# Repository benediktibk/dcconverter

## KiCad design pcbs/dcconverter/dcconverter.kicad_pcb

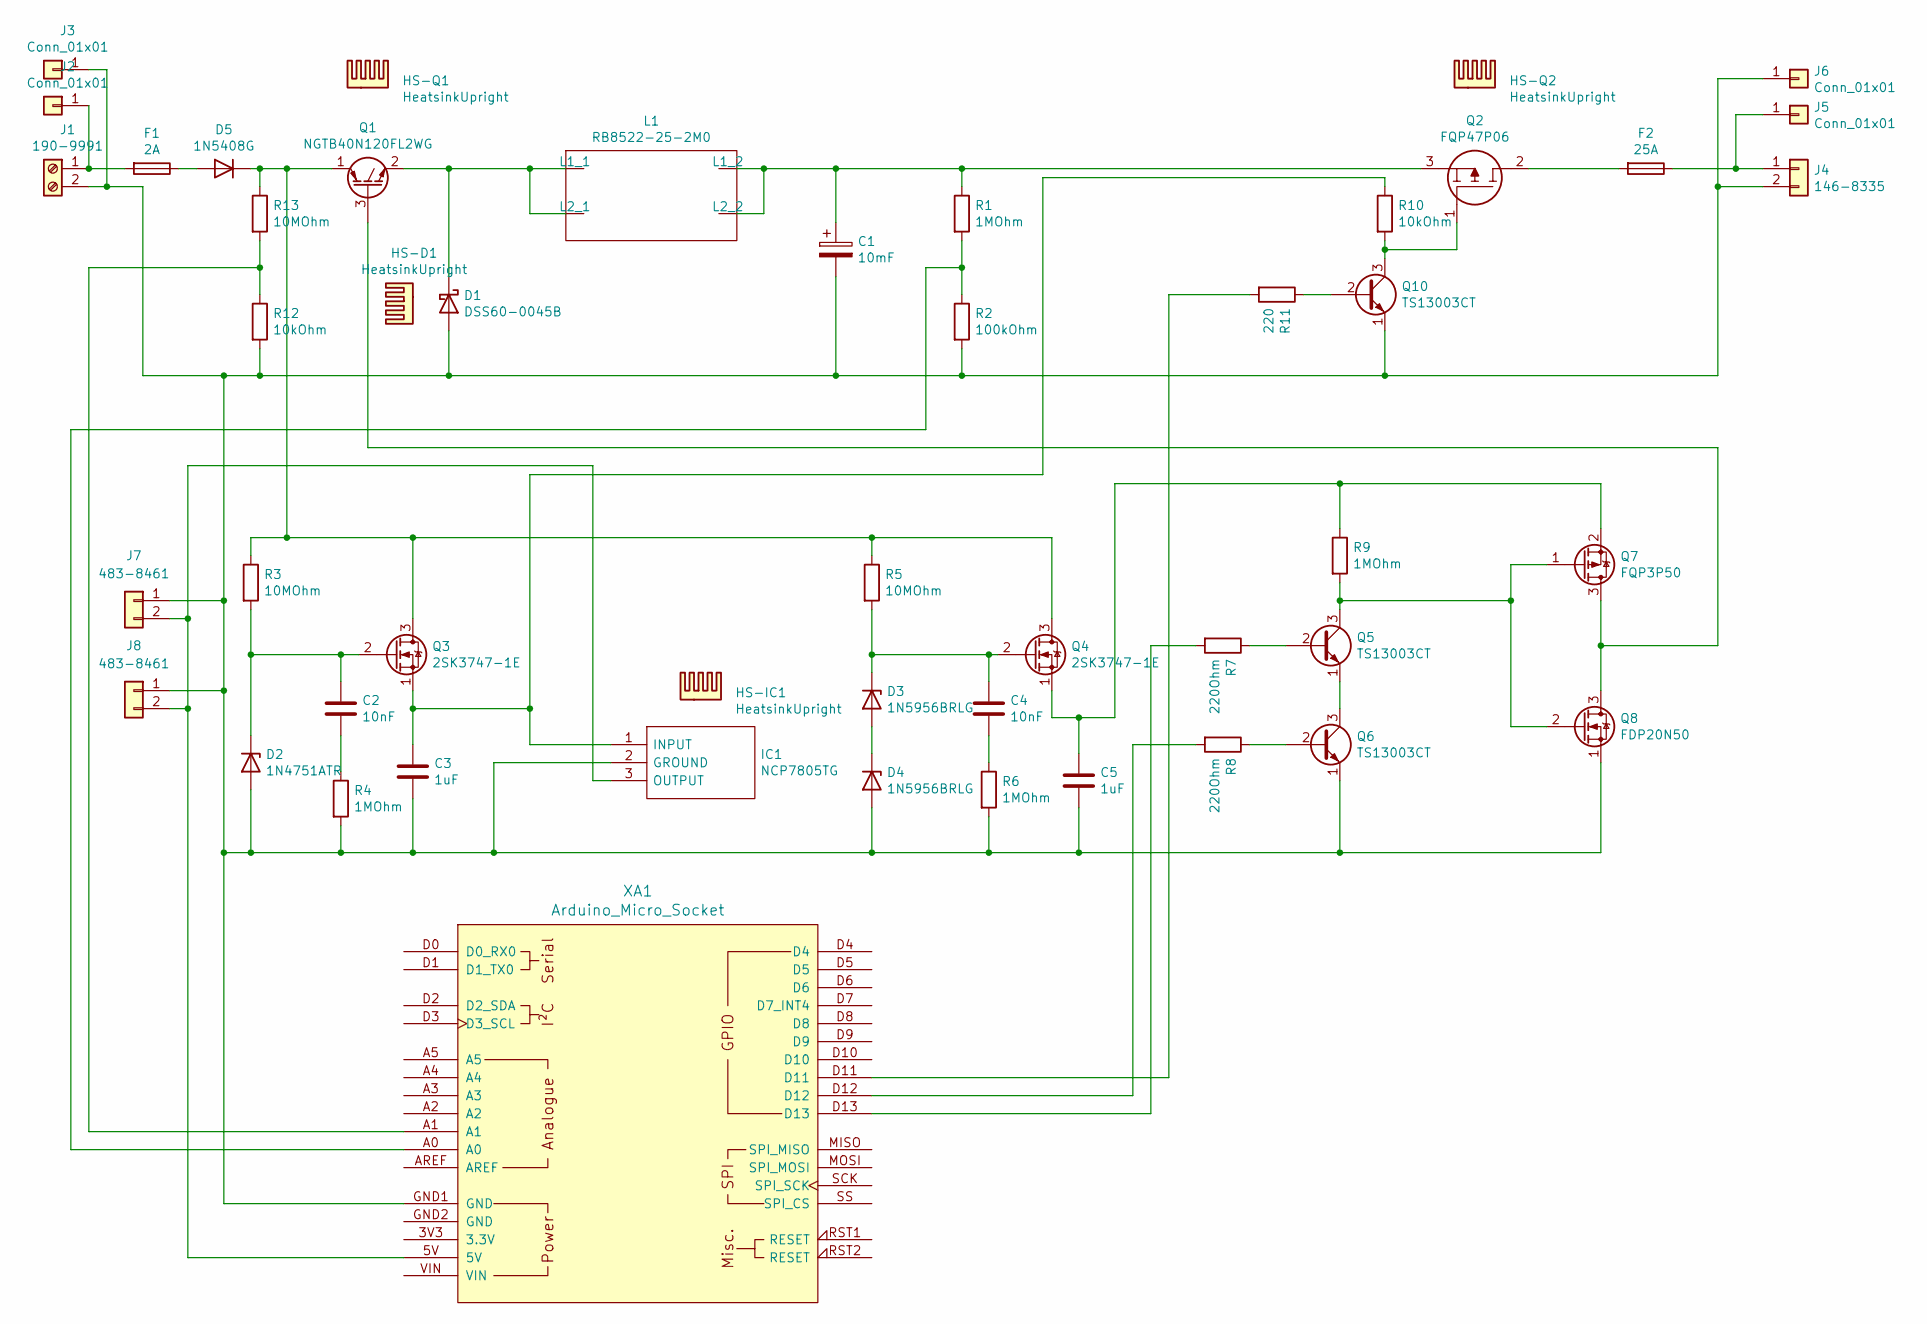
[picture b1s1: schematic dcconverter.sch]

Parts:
C1: 10mF; CAPPRD1250W100D2550H5200
C2, C4: 10nF; C_Disc_D14.5mm_W5.0mm_P7.50mm
C3, C5: 1uF; CP_Radial_D8.0mm_P2.50mm
D1: DSS60-0045B; DSS60-0045B_Vertical
D2: 1N4751ATR; D_DO-41_SOD81_P10.16mm_Horizontal
D3, D4: 1N5956BRLG; D_DO-41_SOD81_P10.16mm_Horizontal
D5: 1N5408G
F1: 2A; Fuseholder_Cylinder-5x20mm_Schurter_0031_8201_Horizontal_Op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
F2: 25A; Fuseholder_Cylinder-5x20mm_Schurter_0031_8201_Horizontal_Op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
HS-D1: HeatsinkUpright
HS-IC1: HeatsinkUpright
HS-Q1, HS-Q2: HeatsinkUpright
IC1: NCP7805TG; TO-220-3_Vertical; Manufacturer_Part_Number NCP7805TG
J1: 190-9991; TerminalBlock_2pin_10mm
J2, J3, J5, J6: Conn_01x01; SLB4-I90
J4: 146-8335; connector_2pin_P10.6mm
J7, J8: 483-8461; Molex_KK_254_2pin
L1: RB8522-25-2M0; rb8522_size5
Q1: NGTB40N120FL2WG; NGTB40N120FL2WG_Vertical
Q2: FQP47P06; FQP47P06_Vertical_Wide; Manufacturer_Part_Number FQP47P06
Q3, Q4: 2SK3747-1E; 2SK3747_TabDown
Q5, Q6, Q10: TS13003CT; TS13003CT_wide
Q7: FQP3P50; FQP3P50_Horizontal_TabDown
Q8: FDP20N50; FDP20N50_Horizontal_TabDown
R1, R4, R6, R9: 1MOhm; R_Axial_DIN0207_L6.3mm_D2.5mm_P10.16mm_Horizontal
R2: 100kOhm; R_Axial_DIN0207_L6.3mm_D2.5mm_P10.16mm_Horizontal
R3, R5, R13: 10MOhm; R_Axial_DIN0207_L6.3mm_D2.5mm_P10.16mm_Horizontal
R7, R8: 220Ohm; R_Axial_DIN0207_L6.3mm_D2.5mm_P10.16mm_Horizontal
R10, R12: 10kOhm; R_Axial_DIN0207_L6.3mm_D2.5mm_P10.16mm_Horizontal
R11: 220; R_Axial_DIN0207_L6.3mm_D2.5mm_P10.16mm_Horizontal
XA1: Arduino_Micro_Socket

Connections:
unnamed: C1.1, L1.3 (L1_2), L1.4 (L2_2), Q2.3, R1.1
unnamed: C1.2, C3.2, C5.2, D1.2 (A), D2.2 (A), D4.2 (A), IC1.2 (GROUND), J1.2, J3.1, J4.2, J6.1, J7.1, J8.1, Q6.1 (E), Q8.1 (S), Q10.1 (E), R2.2, R4.2, R6.2, R12.2, XA1.GND1 (GND)
unnamed: C2.1, D2.1 (K), Q3.2 (G), R3.2
unnamed: C2.2, R4.1
unnamed: C3.1, IC1.1 (INPUT), Q3.1 (S), R10.1
unnamed: C4.1, D3.1 (K), Q4.2 (G), R5.2
unnamed: C4.2, R6.1
unnamed: C5.1, Q4.1 (S), Q7.2 (S), R9.1
unnamed: D1.1 (K), L1.1 (L1_1), L1.2 (L2_1), Q1.2 (E)
unnamed: D3.2 (A), D4.1 (K)
unnamed: D5.1 (K), Q1.1 (C), Q3.3 (D), Q4.3 (D), R3.1, R5.1, R13.1
unnamed: D5.2 (A), F1.1
unnamed: F1.2, J1.1, J2.1
unnamed: F2.1, J4.1, J5.1
unnamed: F2.2, Q2.2
unnamed: IC1.3 (OUTPUT), J7.2, J8.2, XA1.5V
unnamed: Q1.3 (G), Q7.3 (D), Q8.3 (D)
unnamed: Q5.1 (E), Q6.3 (C)
unnamed: Q5.2 (B), R7.1
unnamed: Q5.3 (C), Q7.1 (G), Q8.2 (G), R9.2
unnamed: Q6.2 (B), R8.1
unnamed: Q10.2 (B), R11.1
unnamed: Q2.1, Q10.3 (C), R10.2
unnamed: R1.2, R2.1, XA1.A0
unnamed: R7.2, XA1.D13
unnamed: R8.2, XA1.D12
unnamed: R11.2, XA1.D11
unnamed: R12.1, R13.2, XA1.A1

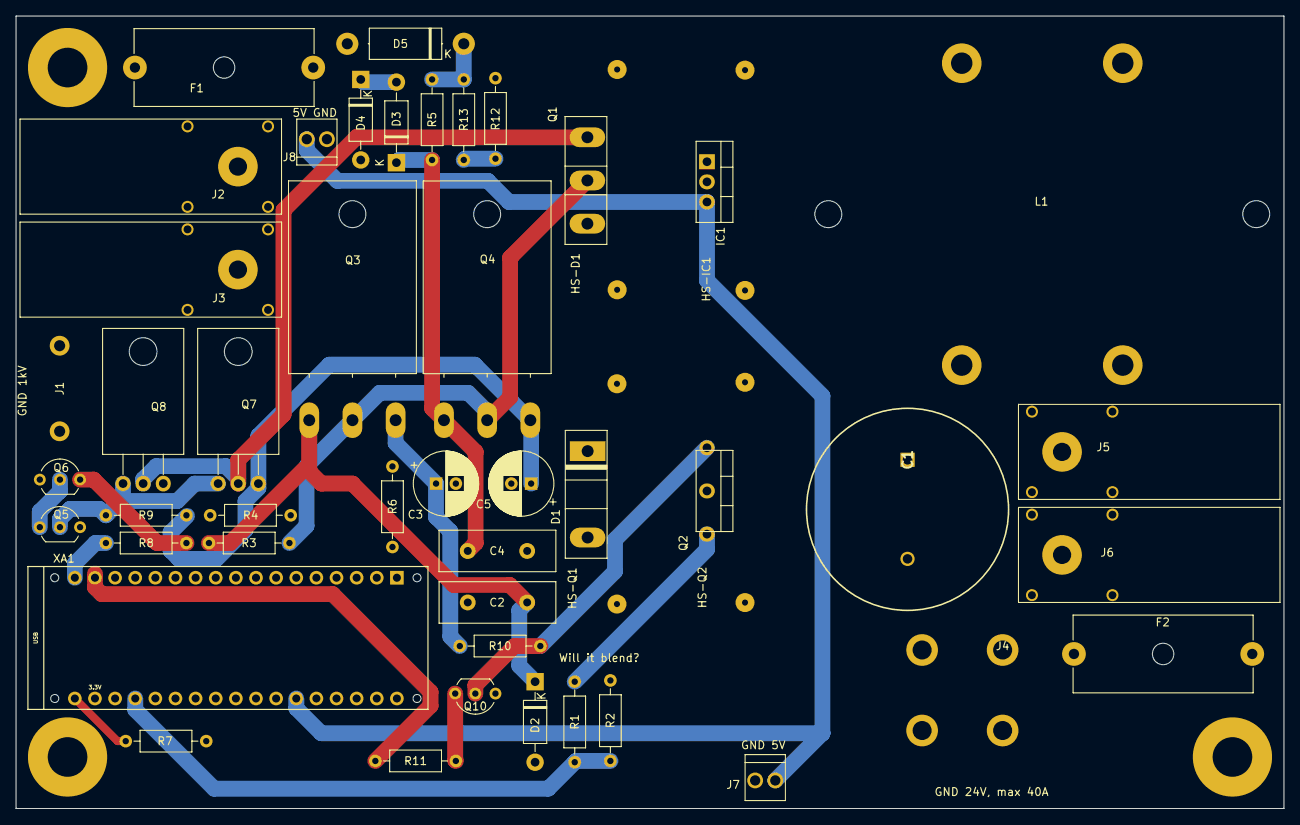
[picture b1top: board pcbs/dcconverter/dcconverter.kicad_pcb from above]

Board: 4 copper layers, 160.0 x 100.0 mm, 49 parts (0 on the bottom side), 28 nets.

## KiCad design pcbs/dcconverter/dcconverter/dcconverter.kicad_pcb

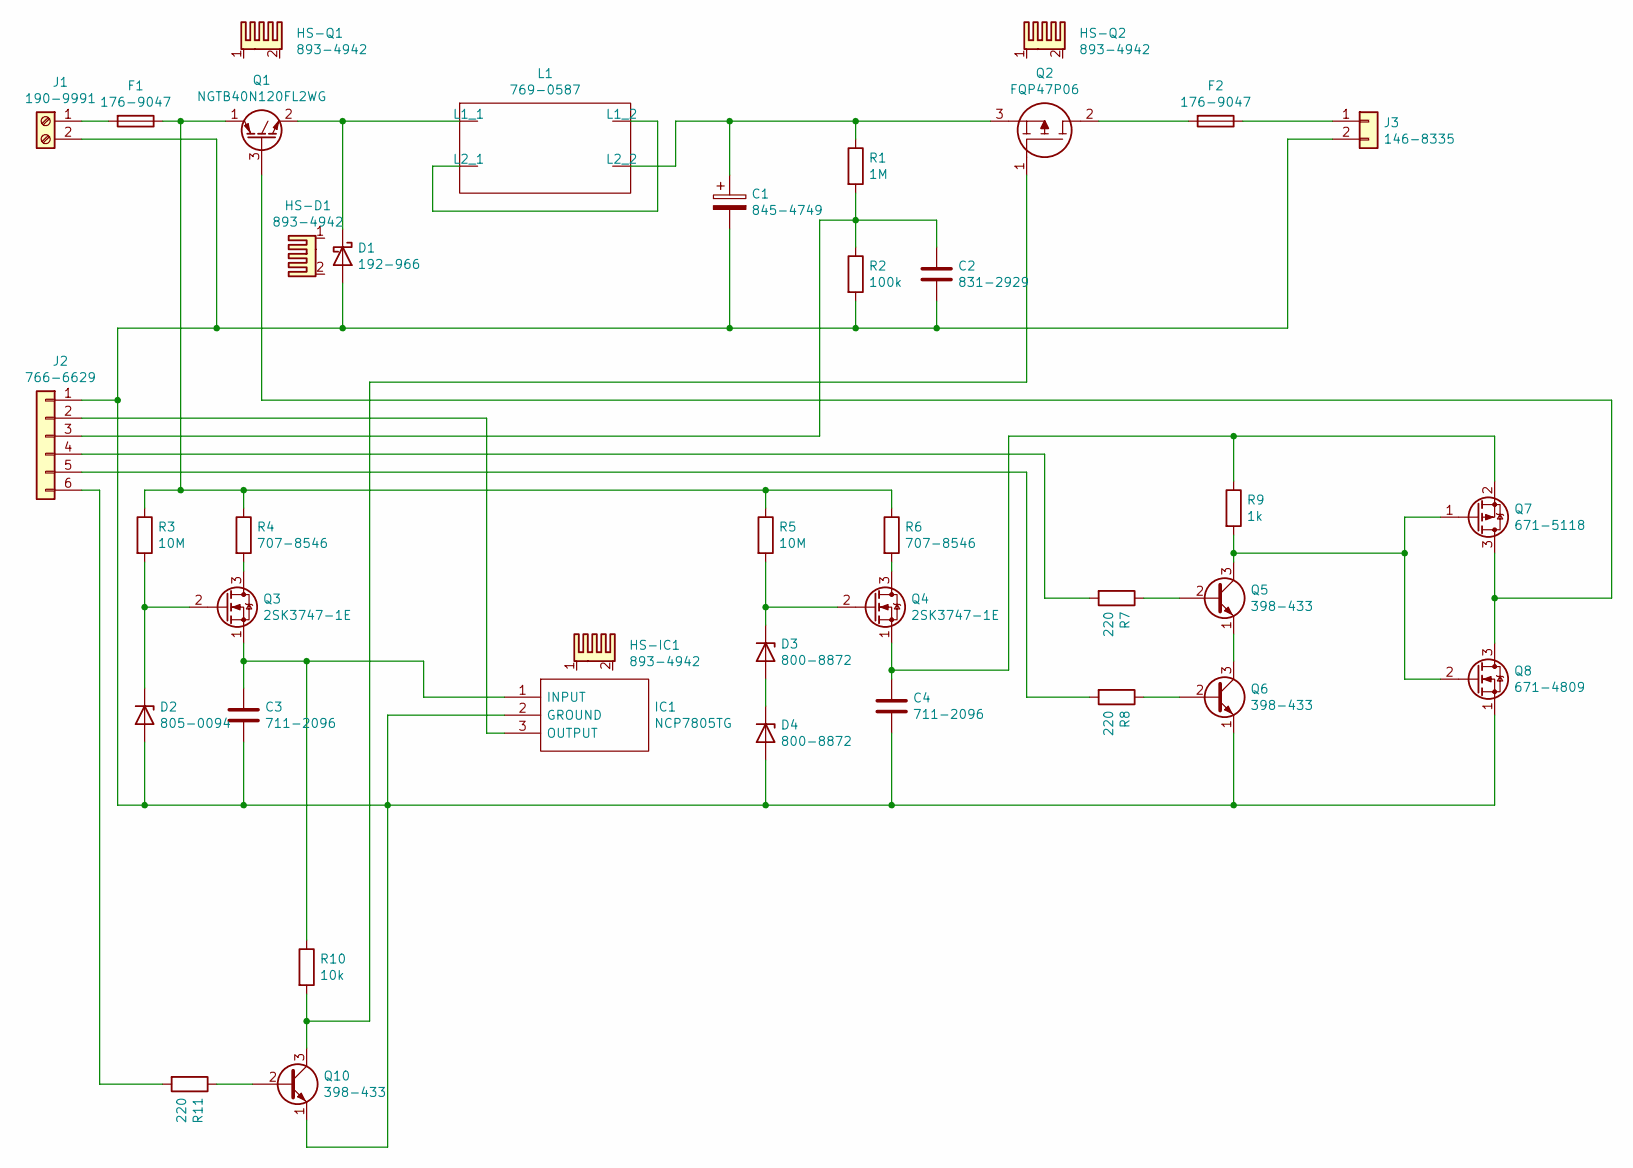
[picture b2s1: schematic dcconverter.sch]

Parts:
C1: 845-4749; CAPPRD1250W100D2550H5200
C2: 831-2929; C_Disc_D7.5mm_W5.0mm_P7.50mm
C3, C4: 711-2096; C_Disc_D7.5mm_W5.0mm_P7.50mm
D1: 192-966; D_DO-247_Vertical
D2: 805-0094; D_DO-41_SOD81_P10.16mm_Horizontal
D3, D4: 800-8872; D_DO-41_SOD81_P10.16mm_Horizontal
F1, F2: 176-9047; Fuseholder_Cylinder-5x20mm_Schurter_0031_8201_Horizontal_Op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
HS-D1: 893-4942; Heatsink_Fischer_SK129-STS_42x25mm_2xDrill2.5mm
HS-IC1: 893-4942; Heatsink_Fischer_SK129-STS_42x25mm_2xDrill2.5mm
HS-Q1, HS-Q2: 893-4942; Heatsink_Fischer_SK129-STS_42x25mm_2xDrill2.5mm
IC1: NCP7805TG; TO-220-3_Vertical; Manufacturer_Part_Number NCP7805TG
J1: 190-9991; TerminalBlock_Dinkle_DT-55-B01X-02_P10.00mm
J2: 766-6629; CES-106-XX-Y-S
J3: 146-8335; connector_2pin_P10.6mm
L1: 769-0587; rb8522_size5
Q1: NGTB40N120FL2WG; TO-247-3_Vertical
Q2: FQP47P06; TO254P483X1016X2261-3P; Manufacturer_Part_Number FQP47P06
Q3, Q4: 2SK3747-1E; TO-3P-3_Horizontal_TabDown
Q5, Q6, Q10: 398-433; TO-92_Inline
Q7: 671-5118; TO-220-3_Horizontal_TabDown
Q8: 671-4809; TO-3P-3_Horizontal_TabDown
R1: 1M; R_Axial_DIN0207_L6.3mm_D2.5mm_P10.16mm_Horizontal
R2: 100k; R_Axial_DIN0207_L6.3mm_D2.5mm_P10.16mm_Horizontal
R3, R5: 10M; R_Axial_DIN0207_L6.3mm_D2.5mm_P10.16mm_Horizontal
R4, R6: 707-8546; R_Axial_DIN0207_L6.3mm_D2.5mm_P10.16mm_Horizontal
R7, R8, R11: 220; R_Axial_DIN0207_L6.3mm_D2.5mm_P10.16mm_Horizontal
R9: 1k; R_Axial_DIN0207_L6.3mm_D2.5mm_P10.16mm_Horizontal
R10: 10k; R_Axial_DIN0207_L6.3mm_D2.5mm_P10.16mm_Horizontal

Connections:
unnamed: C1.1, L1.4 (L2_2), Q2.3, R1.1
unnamed 1: C1.2, C2.2, C3.2, C4.2, D1.2 (A), D2.2 (A), D4.2 (A), IC1.2 (GROUND), J1.2, J2.1, J3.2, Q6.1 (E), Q8.1 (S), Q10.1 (E), R2.2; also elsewhere on the board
unnamed: C2.1, J2.3, R1.2, R2.1
unnamed: C3.1, IC1.1 (INPUT), Q3.1 (S), R10.1
unnamed: C4.1, Q4.1 (S), Q7.2 (S), R9.1
unnamed: D1.1 (K), L1.1 (L1_1), Q1.2 (E)
unnamed: D2.1 (K), Q3.2 (G), R3.2
unnamed: D3.1 (K), Q4.2 (G), R5.2
unnamed: D3.2 (A), D4.1 (K)
unnamed: F1.1, Q1.1 (C), R3.1, R4.1, R5.1, R6.1
unnamed: F1.2, J1.1
unnamed: F2.1, J3.1
unnamed: F2.2, Q2.2
unnamed 17: IC1.3 (OUTPUT), J2.2; also elsewhere on the board
unnamed: J2.4, R7.2
unnamed: J2.5, R8.2
unnamed: J2.6, R11.2
unnamed: L1.2 (L2_1), L1.3 (L1_2)
unnamed: Q1.3 (G), Q7.3 (D), Q8.3 (D)
unnamed: Q3.3 (D), R4.2
unnamed: Q4.3 (D), R6.2
unnamed: Q5.1 (E), Q6.3 (C)
unnamed: Q5.2 (B), R7.1
unnamed: Q5.3 (C), Q7.1 (G), Q8.2 (G), R9.2
unnamed: Q6.2 (B), R8.1
unnamed: Q10.2 (B), R11.1
unnamed: Q2.1, Q10.3 (C), R10.2

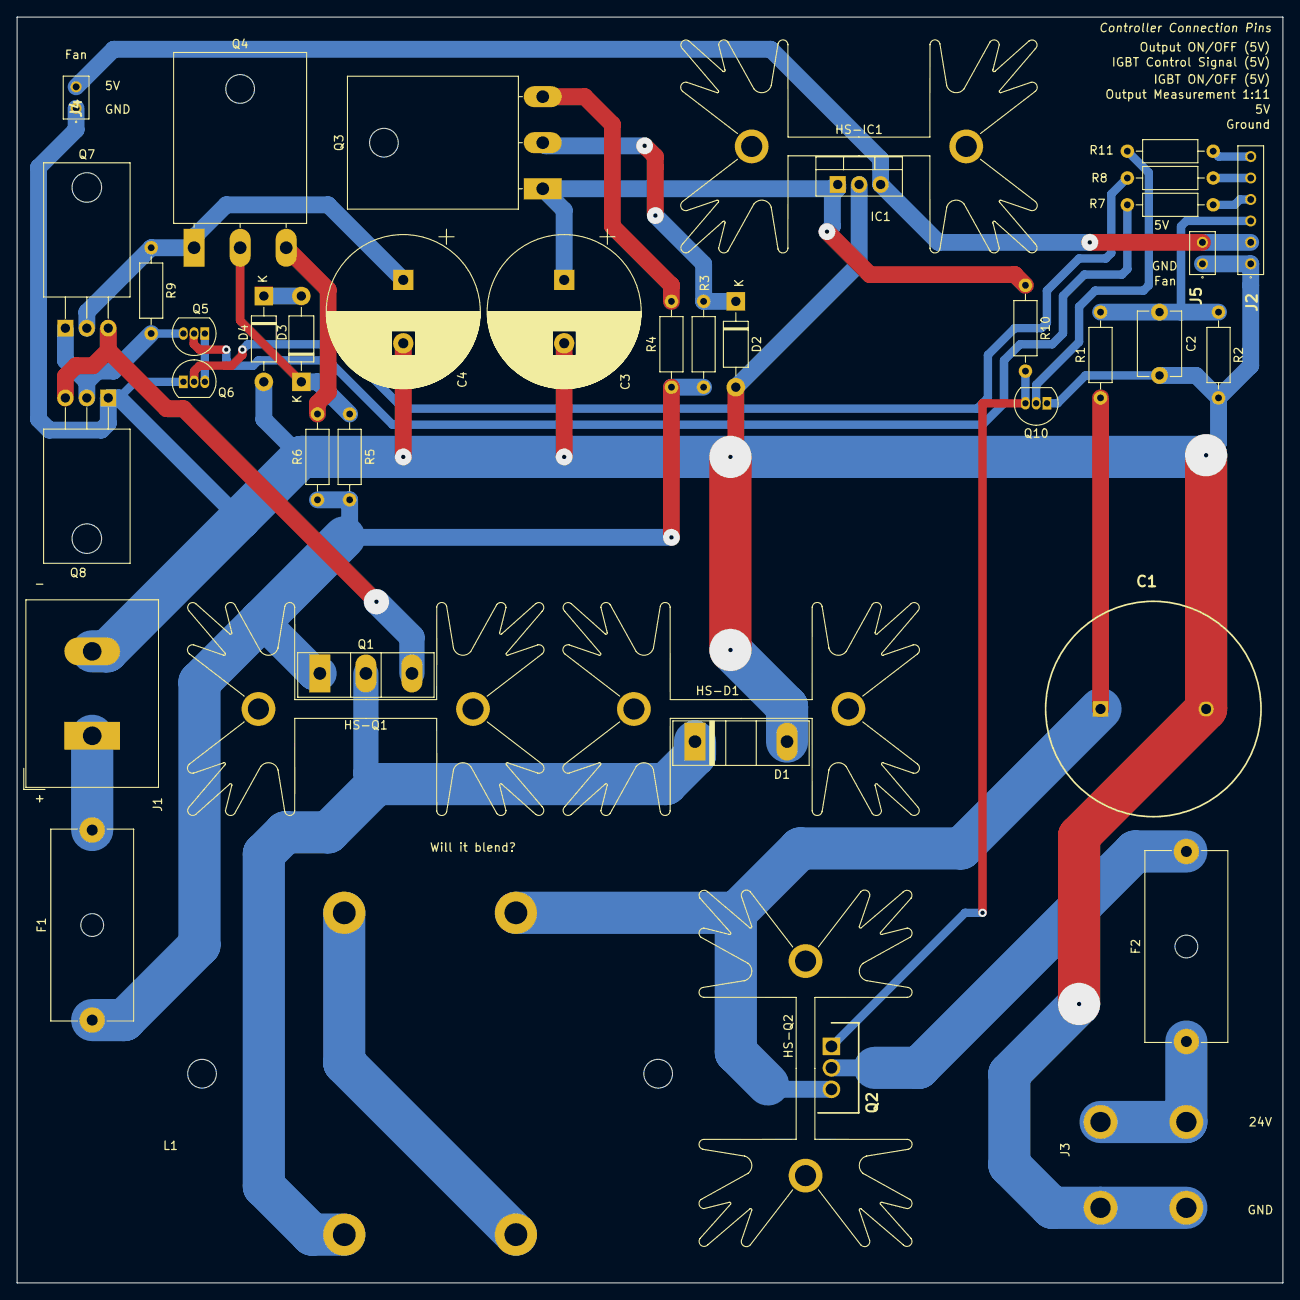
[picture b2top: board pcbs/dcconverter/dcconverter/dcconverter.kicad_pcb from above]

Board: 2 copper layers, 149.9 x 149.9 mm, 41 parts (0 on the bottom side), 27 nets.

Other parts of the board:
J4, J5: 766-6604; CES-102-XX-Y-S

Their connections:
unnamed 1: J4.1, J5.1; also elsewhere on the board
unnamed 17: J4.2, J5.2; also elsewhere on the board

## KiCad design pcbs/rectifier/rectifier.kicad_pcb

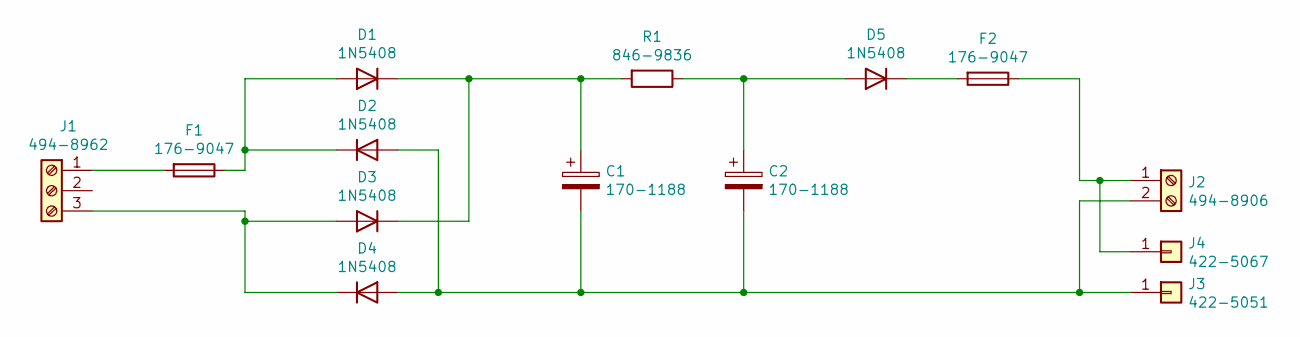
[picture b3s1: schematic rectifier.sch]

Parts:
C1, C2: 170-1188; CP_Radial_D18.0mm_P7.50mm
D1, D2, D3, D4, D5: 1N5408; D_DO-201AD_P15.24mm_Horizontal
F1, F2: 176-9047; Fuseholder_Cylinder-5x20mm_Schurter_0031_8201_Horizontal_Op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
J1: 494-8962; TerminalBlock_Altech_AK300-3_P5.00mm
J2: 494-8906; TerminalBlock_Altech_AK300-2_P5.00mm
J3: 422-5051; SLB4-I90
J4: 422-5067; SLB4-I90
R1: 846-9836; R_Axial_DIN0414_L11.9mm_D4.5mm_P15.24mm_Horizontal

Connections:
unnamed: C1.1, D1.1 (K), D3.1 (K), R1.2
unnamed: C1.2, C2.2, D2.2 (A), D4.2 (A), J2.2, J3.1
unnamed: C2.1, D5.2 (A), R1.1
unnamed: D1.2 (A), D2.1 (K), F1.1
unnamed: D3.2 (A), D4.1 (K), J1.3
unnamed: D5.1 (K), F2.2
unnamed: F1.2, J1.1
unnamed: F2.1, J2.1, J4.1

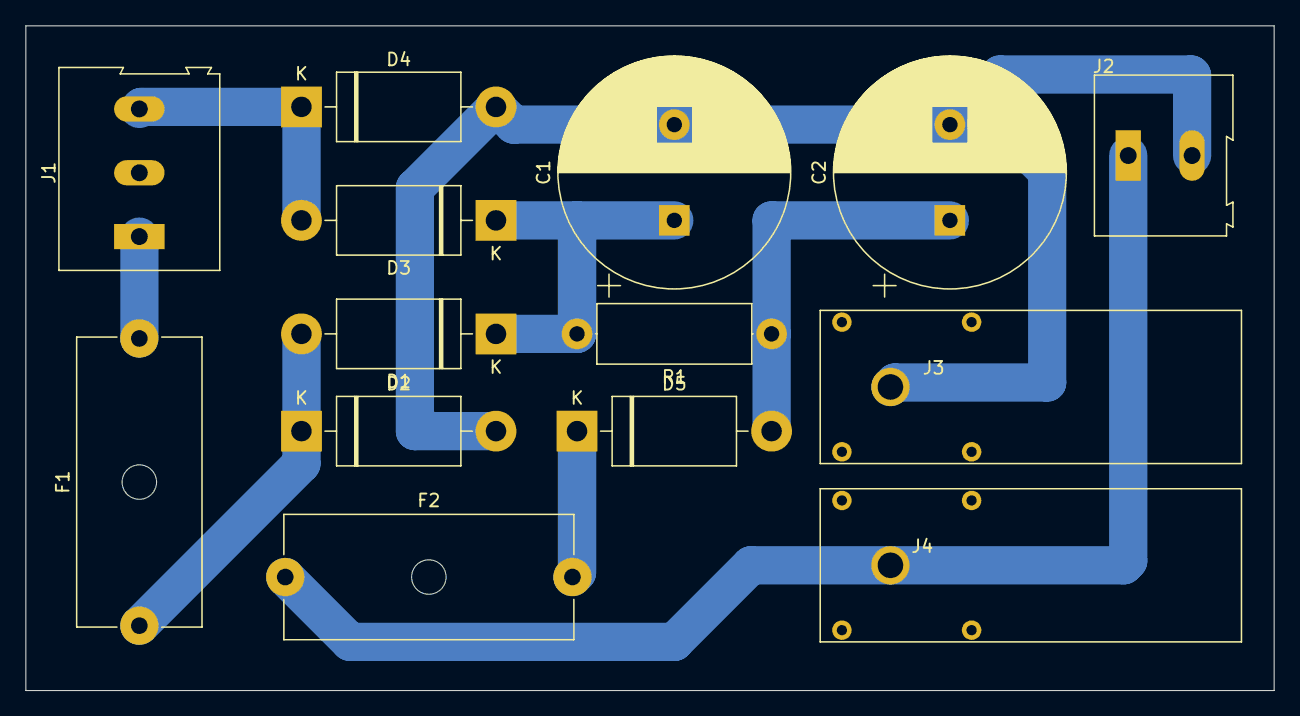
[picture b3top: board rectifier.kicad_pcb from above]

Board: 2 copper layers, 97.8 x 52.1 mm, 14 parts (0 on the bottom side), 8 nets.

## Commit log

2019-03-26 Add previous work
2019-03-26 Ignore .net Files
2019-03-27 Implement simple controller version
2019-03-27 Rename Schematics
2019-03-27 Simplify Controller
2019-04-02 Add circuit sizing
2019-04-02 Add basic Arduino Project
2019-04-02 Add Example Pulse Width Modulation Circuit
2019-04-02 Add Prototype with lower Voltages
2019-04-02 Implement Controller for Low Voltage Prototype
2019-07-23 Add Simulation in Python
2019-07-23 Fix formula for circuit
2019-07-23 Add Visual Studio Code Config
2019-10-17 Add Measurements
2019-12-02 Add Test Circuit for only resistors
2019-12-02 Add Simulation for ResistorInSeries
2019-12-02 Add Testcase for additional Capacitor
2019-12-02 Turn the input voltage into a static parameter of the circuit
2019-12-02 First try to implement the circuit with Capacitor
2019-12-03 Add Testcase for ResistorInSeriesAndInductance
2019-12-03 Implement ResistorInSeriesAndInductance
2019-12-03 Fix Tests for ResistorInSeriesAndInductance
2019-12-03 Add Test for ResistorInSeriesAndCapacitor
2019-12-03 Ignore .plt Files
2019-12-03 Fix ResistorInSeriesAndCapacitor
2019-12-03 Add Tests for StepDownConverter
2019-12-03 Implement StepDownConverter
2019-12-03 Add Test for Aperiodic Stepdown Converter
2019-12-03 Add Function to calculate Gradients
2019-12-03 Reduce redundant Calculations in StepDownConverter
2019-12-03 Separate aperiodic and periodic case in StepDownConverter
2019-12-03 Add Tests for sequential Circuit use
2019-12-03 Implement Gradient Calculation for periodic Case
2019-12-03 Implement Gradient Calculation for aperiodic Case
2019-12-03 Introduce Dto for Circuit Data
2019-12-03 Rename Interface
2019-12-03 Fix test for aperiodic StepDownConverter
2019-12-03 Fix Test for StepDownConverter
2019-12-03 Add Test for Gradient Calculation
2019-12-03 Fix Tests for StepDownConverter
2019-12-04 Remove Python-Approach for the Controller Optimization
2019-12-04 Reduce Directory Nesting
2019-12-04 Add Infrastructure for StepDownConverterTest
2019-12-04 Set realistic Values for Test of StepDownConverter
2019-12-04 Implement StepDownConverter Simulation
2019-12-04 Add Tests for ConstantInputVoltage
2019-12-04 Add Tests for ConstantOnOffController
2019-12-04 Fix ConstantOnOffController
2019-12-04 Fix endless loop in StepDownConverter
2019-12-04 Fix Calculation of next time Step in ConstantOnOffController
2019-12-04 Fix Remainder Calculation in ConstantOnOffController
2019-12-04 Improve Performance of StepDownConverter
2019-12-04 Add Test for StepDownConverter
2019-12-04 Improve Tests for StepDownConverter
2019-12-04 Rename Classes and Files with the Suffix Simulator to distinguish between Circuit and Converter
2019-12-04 Add Test for StepDownConverterCircuitSimulator
2019-12-04 Improve Test
2019-12-04 Fix Name of Test
2019-12-04 Fix Tests
2019-12-04 Fix Tests for StepDownConverterSimulator
2019-12-04 Fix calculation of values in StepDownConverterSimulator
2019-12-04 Fix value in Test
2019-12-04 Add Tests for StepDownConverterCircuitSimulator
2019-12-04 Improve Tests
2019-12-08 Simplify Calculations
2019-12-08 Add File Output for Debugging Purpose
2019-12-08 Add Test with complete Data Series
2019-12-08 Fix Matching of Data Series
2019-12-08 Add Test for Matching of Data Series
2019-12-08 Fix Parsing of Data Series
2019-12-08 Fix Test for CircuitSimulator
2019-12-08 Fix Test
2019-12-08 Remove output to File in Test
2020-09-21 Reduce available version to only one
2020-09-21 Use real world values for circuit simulation
2020-09-21 Improve values
2020-09-21 Found reasonable values
2020-09-21 Improve Driver
2020-09-21 Work on Driver
2020-09-22 Use CMOS Inverter to drive the IGBT Gate
2020-09-22 Add Example circuit for IGBT Gate Driver
2020-09-22 Work on Gate Driver Circuit
2020-09-23 Implement Driver with Input Voltage of 100V
2020-09-23 Change Gate Driver to a CMOS inverter with max 500V
2020-09-23 Test Reduction of Control Voltage to 100V
2020-09-23 Use a Mosfet as the Gate Voltage Source
2020-09-23 Make it possible to control the IGBT with 20V
2020-09-23 Control the IGBT gate with 5V
2020-09-23 Separate Gate Driver
2020-09-23 Find timing setup for approximately 24 Volt output
2020-09-23 Implement Controller
2020-09-23 Added separate Controller
2020-09-23 Test different Values for Controller
2020-09-23 Use default NMOS for simulation to speed it up
2020-09-23 Figured out correct Timings for Controller
2020-09-23 Add Graph for Output Voltage/Period Time
2020-09-23 Set reasonable Values in Controller
2020-09-24 Improve DC DC Converter itself
2020-09-24 Simplify DC DC Converter
2020-09-24 Fill in more realistic values for the inductance and the capacitor
2020-09-24 Improve DC DC Converter
2020-09-24 fine tune values
2020-10-09 Implement Controller with Usage of Timer
2020-10-09 Use high speed timer
2020-10-09 Configure Timer correctly
2020-10-09 Manually write the Output Pin
2020-10-09 Set Output Bits directly via a Macro to speed it up
2020-10-10 Use direct output OC4A instead of interrupts
2020-10-11 Make the Controller configurable
2020-10-11 Implement basic P-Controller
2020-10-11 Figure out a somewhat reasonable value for kp
2020-10-11 Implement PI controller
2020-10-11 Invert Output on Hardware once more
2020-10-13 Reduce maximum cumulative error
2020-10-14 Add Circuit Design for B2 Rectifier
2020-10-14 Add PCB for Rectifier
2020-10-15 Apply Knowledge learned from Prototype to Driver
2020-10-22 Add Gate for Controller in Simulation
2020-10-22 Start with adding an Output-IGBT to the Simulation
2020-10-22 Set the output gate with the Controller
2020-10-22 Simplify output high side switch
2020-10-22 Test high side switch
2020-10-22 Fix output high side switch
2020-10-22 Make minor tweaks to the Converter Circuit Design
2020-10-22 Use different Inductor
2020-10-23 Add PCB Design for DC Converter
2020-10-24 Wire Two Phase Inductor differently
2020-10-24 Simplify driver for IGBT
2020-10-24 Change used Inductor in Simulation of DC Converter
2020-10-24 Finish Schematic for PCB
2020-10-24 Start with routing of DC Converter
2020-10-24 Finish PCB for first draft of DC Converter
2020-10-24 Make Tracks with a high Current as thick as possible
2020-10-26 Note down Todos for PCB
2020-10-26 Reduce additional delay in Control-Loop
2020-10-26 Remove additional dely in Control-Loop completely
2020-10-26 Disable Debug-Logging
2020-11-02 Add Todos
2020-11-03 Minor Changes
2020-11-03 Cleanup Symbol Library
2020-11-03 Cleanup Schematic
2020-11-03 Update Footprints to use Custom PCB Library
2020-11-10 Add item to Todo List
2020-11-16 Reduce Startup Current of Voltage Driver
2020-11-16 Simulate higher Resistor for Gate Driver
2020-11-16 Use correct Symbol and Footprint Libraries
2020-11-16 Convert Todos into Issues on Bitbucket
2020-11-16 Fix Heatsinks
2020-11-16 Fix Footprint for J1
2020-11-16 Improve Voltage Source for Gate Driver
2020-11-16 Fix Issues with Voltage Source in DC DC Converter
2020-11-20 Use correct footprint for Q10
2020-11-20 Use correct footprint for D1
2020-11-20 Use correct footprint for NGTB40N120FL2WG
2020-11-20 Use correct footprint for Q2
2020-11-20 Use correct footprint for Q8
2020-11-20 Use correct footprint for Q7
2020-11-20 Use correct footprint for Q3 and Q4
2020-11-20 Evaluate the two windings in parallel
2020-11-20 Use the windings in parallel
2020-11-20 Add reverse polarity protection
2020-11-20 Add measurement of input voltage
2020-11-20 Fix minor stuff
2020-11-20 Add controller to PCB schematic
2020-11-20 Use in rectifier schematic CP symbol from custom library
2020-11-20 Use footprint of banana socket from custom library in rectifier schematic
2020-11-20 Add banana sockets to DC converter schematic
2020-11-20 Add missing footprints
2020-11-20 Empty PCB
2020-11-21 Use different Capacitor for Voltage Source
2020-11-21 Place PCB
2020-11-21 Improve Placement
2020-11-22 Start routing PCB
2020-11-22 Connect everything in PCB
2020-11-22 Add GND and power planes
2020-11-22 Add power planes
2020-11-22 Improve power planes
2020-11-22 Update Plot for DC Converter
2020-11-22 Remove zip-File of Plots
